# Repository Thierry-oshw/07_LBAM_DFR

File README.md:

# 07_LBAM_DFR
 Boite à Meuh avec du DFR

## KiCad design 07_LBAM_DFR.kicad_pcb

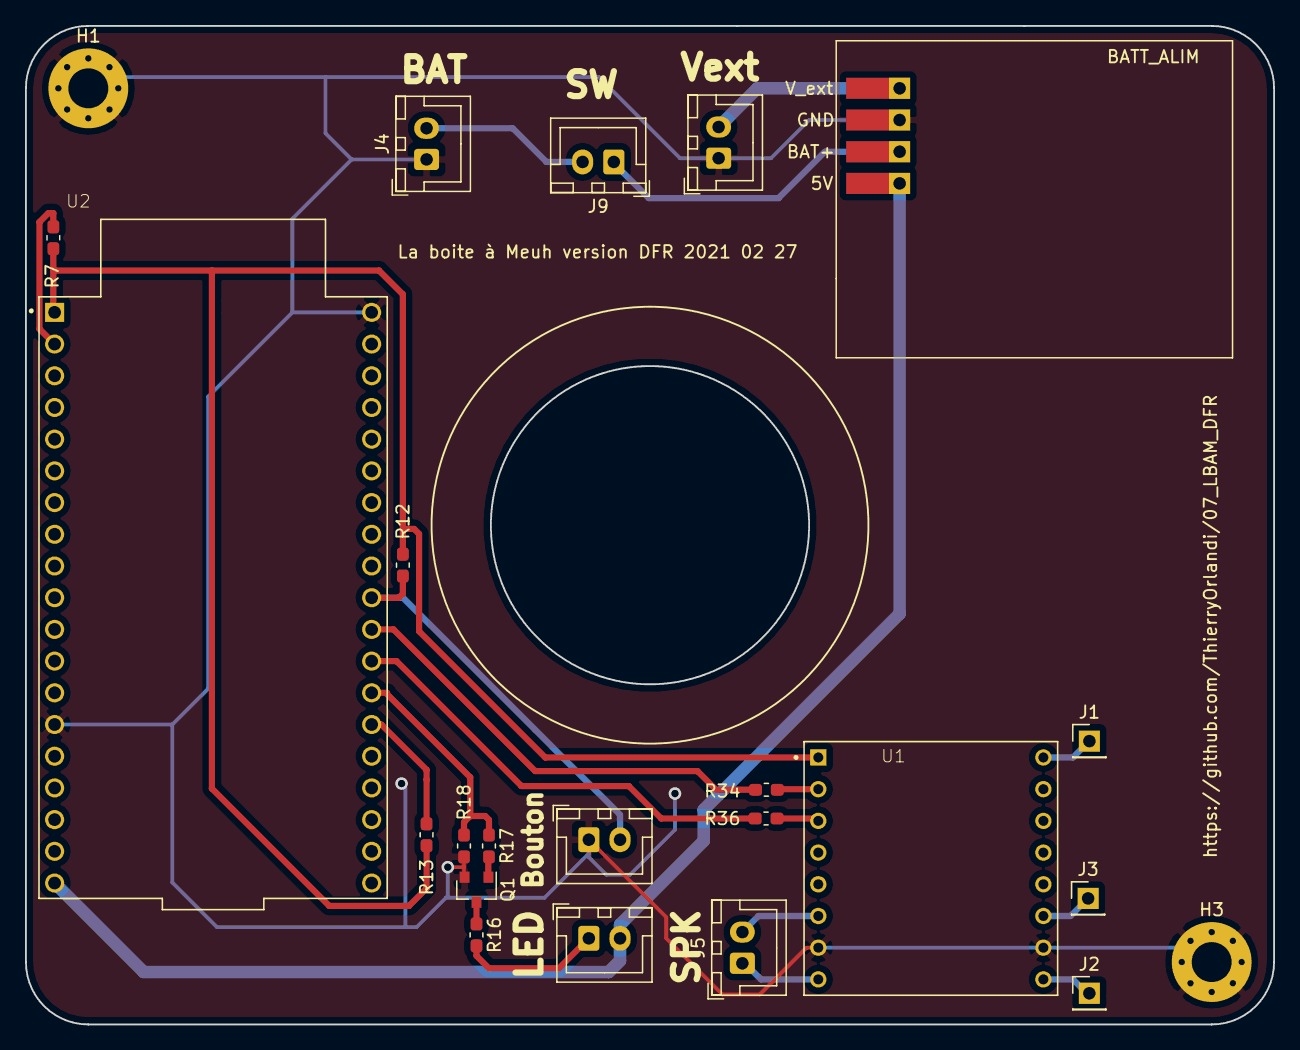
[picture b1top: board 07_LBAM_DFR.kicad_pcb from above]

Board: 2 copper layers, 100.0 x 80.0 mm, 23 parts (0 on the bottom side), 22 nets.

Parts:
H1, H3: MountingHole_Pad; MountingHole_3.2mm_M3_Pad_Via
J1, J2, J3: Conn_01x01; PinHeader_1x01_P2.54mm_Vertical
J4, J5, J9, J18, J26, J27: Conn_01x02; JST_XH_B2B-XH-A_1x02_P2.50mm_Vertical
Q1: 2N7002; SOT-23
R7, R12, R13, R18: 100k; R_0603_1608Metric_Pad1.05x0.95mm_HandSolder
R16, R34, R36: 1k; R_0603_1608Metric_Pad1.05x0.95mm_HandSolder
R17: 100; R_0603_1608Metric_Pad1.05x0.95mm_HandSolder
U1: DFR0299; MODULE_DFR0299
U2: ESP32-DEVKITC; MODULE_ESP32-DEVKITC
U4: Batt_Alim

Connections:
3V3: R7.2, R12.2, R13.1, U1.1, U2.1
5V: J26.2, U2.19, U4.4
/Batt_alim/V_ext: J27.2, U4.1
DFR2ESP: R36.2, U1.3
ESP2DFR: R34.2, U1.2
GND: H1.1, H3.1, J4.1, J18.1, J27.1, Q1.2, R18.1, U1.7, U1.10, U2.14, U2.38, U4.2
LED_out: R17.1, R18.2, U2.26
unnamed: J1.1, U1.16
unnamed: J4.2, J9.2
unnamed: J5.1, U1.8
unnamed: J5.2, U1.6
unnamed: J9.1, U4.3
unnamed: J26.1, R16.2
unnamed: Q1.1, R17.2
unnamed: Q1.3, R16.1
unnamed: R7.1, U2.2
unnamed: R13.2, U2.25
unnamed: R34.1, U2.28
unnamed: R36.1, U2.27
bouton1: J18.2, R12.1, U2.29
next: J2.1, U1.9
prev: J3.1, U1.11

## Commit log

2021-07-24 maj split librairies
2023-05-02 chgt nom fichier licence
